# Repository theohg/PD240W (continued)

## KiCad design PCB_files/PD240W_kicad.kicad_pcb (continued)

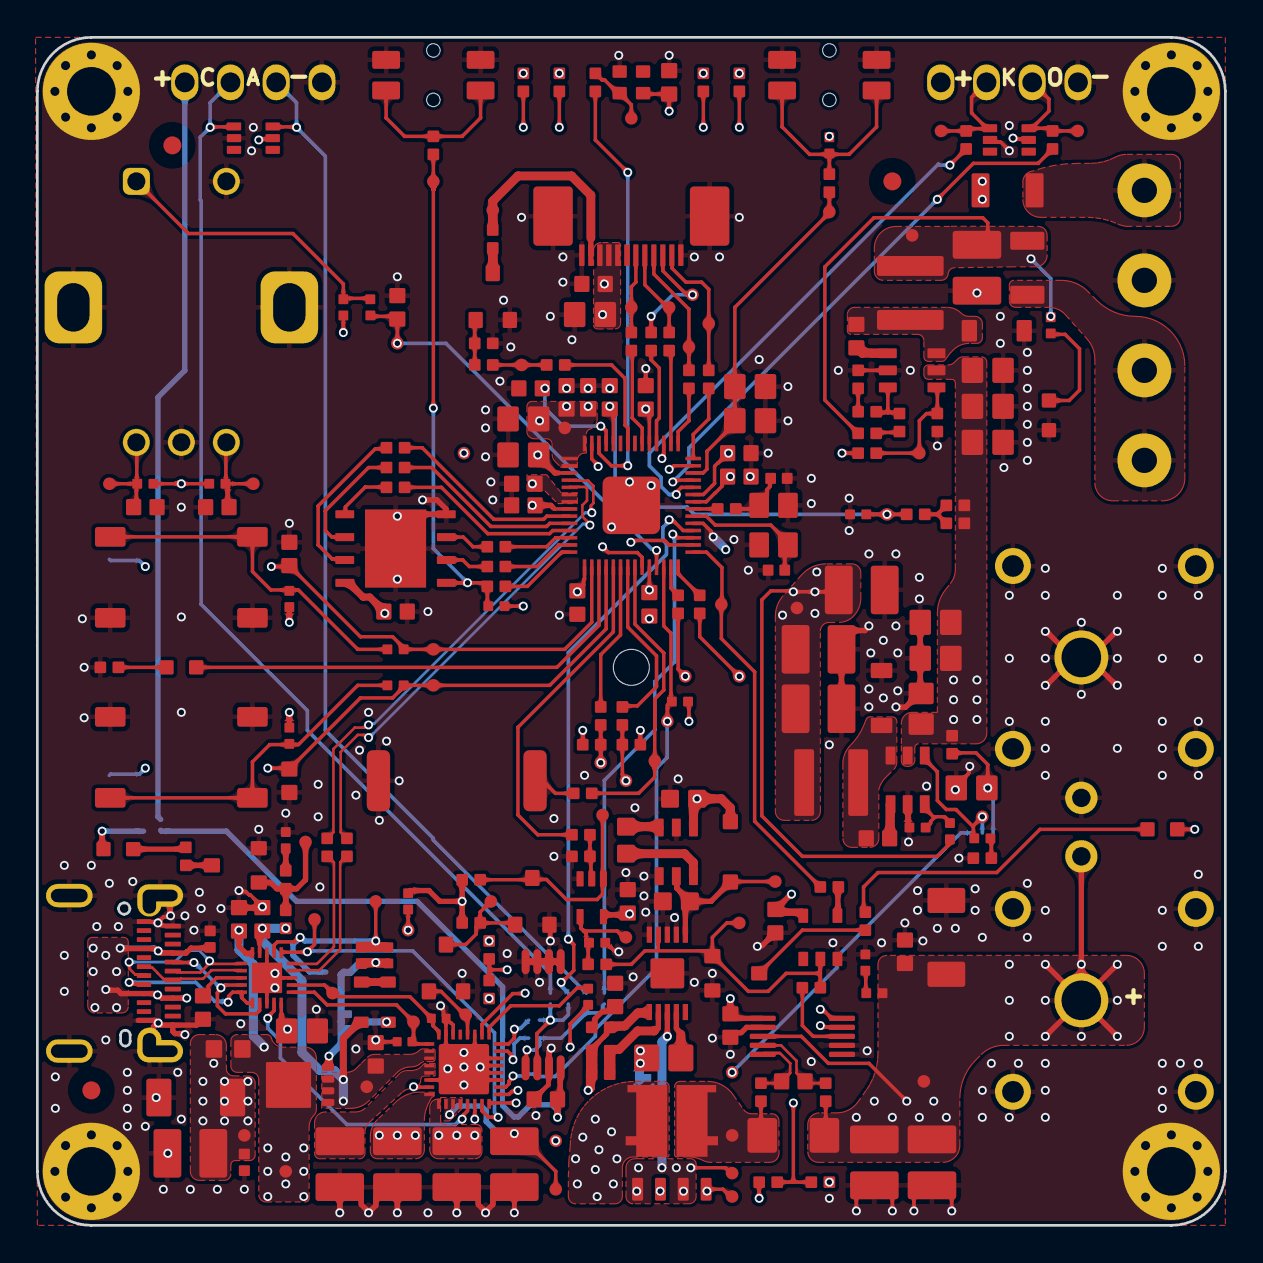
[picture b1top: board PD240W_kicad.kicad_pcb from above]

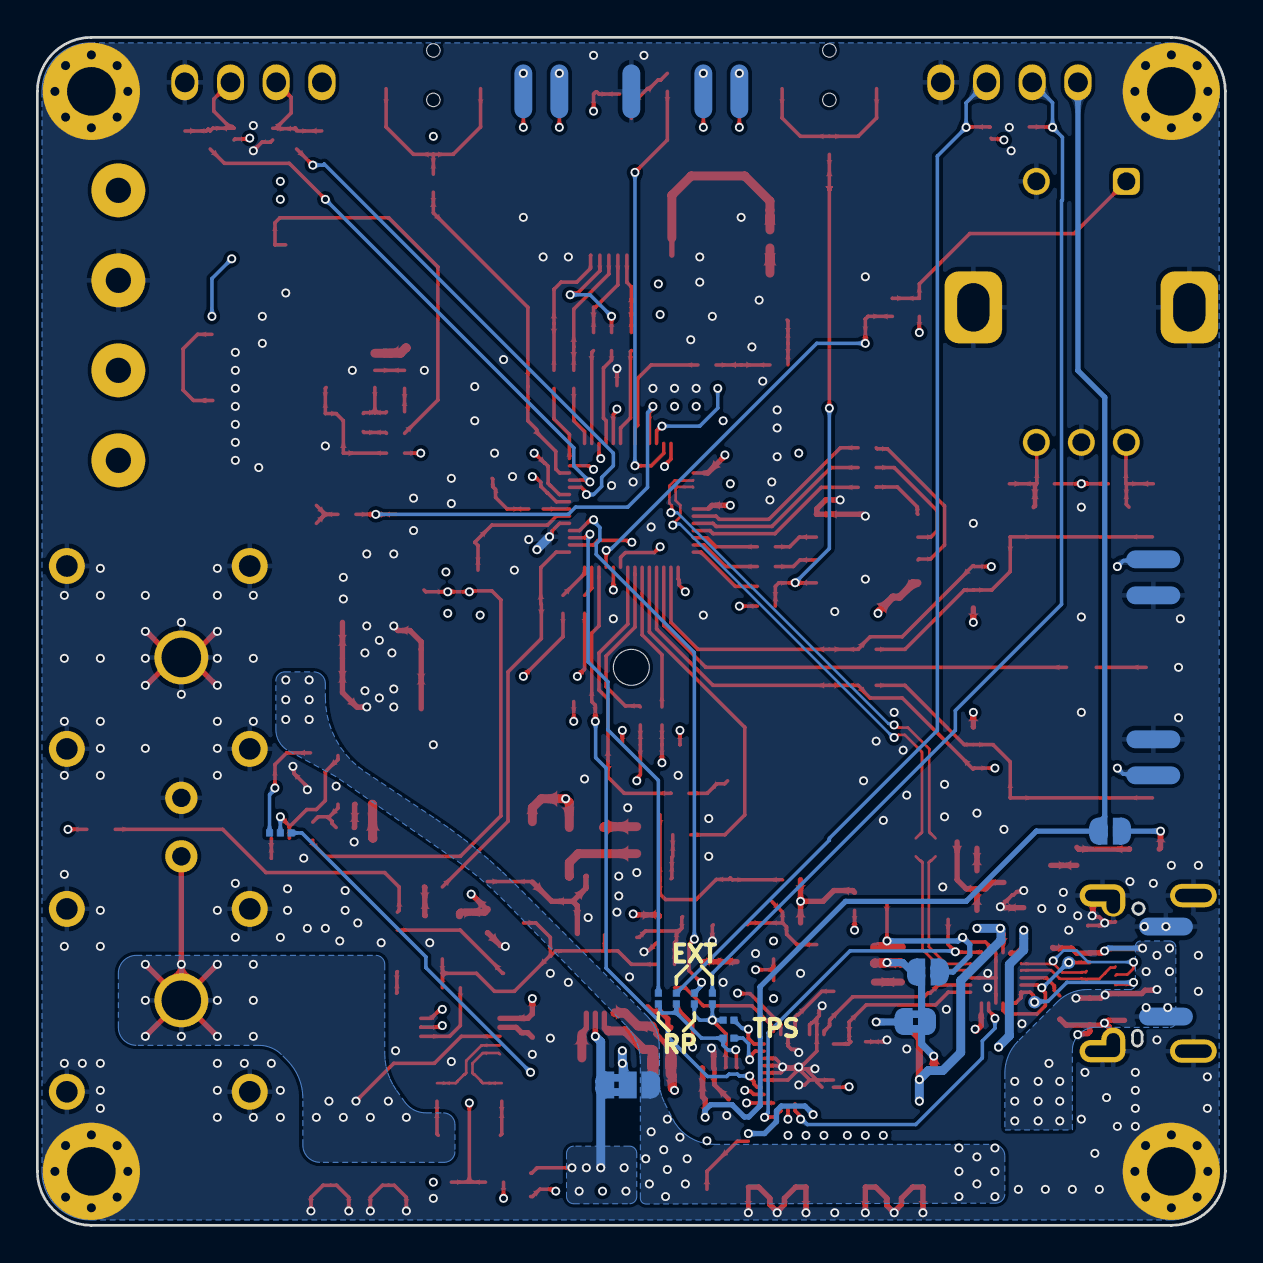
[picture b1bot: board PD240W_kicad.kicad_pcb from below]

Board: 6 copper layers, 66.0 x 66.0 mm, 299 parts (25 on the bottom side), 152 nets.

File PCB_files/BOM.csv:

,Line #,Name,Description,Designator,Quantity,LCSC,Manufacturer 1,Manufacturer Part Number 1
,2,4.7u,"Capacitor, 4.7 uF, 10%, X7S, 100V, 3225, 1210",C3,1,C913445,Murata,GCM32DC72A475KE02K
,3,100n X7R 100V,"Capacitor, 100nF, 10%, X7R, 100V, 1608, 0603","C4, C6, C8, C16, C17, C21, C22, C23, C24, C25, C26, C27, C30, C34, C35, C37, C38, C39, C40, C41, C42, C43, C44, C47, C48, C49, C50, C52, C53, C54, C55, C63",32,C15725,Samsung Electro-Mechanics,CL10B104KC8NNNC
,4,1u X7R 100V,"Capacitor, 1uF, 10%, X7R, 100V, 2012, 0805","C7, C31, C32, C33, C36, C51, C56, C57, C58, C62, C64, C65, C66",13,C5370002,YAGEO,CC0805KKX7R0BB105
,6,3.3u X5R 25V,"Capacitor, 3.3uF, 20%, X5R, 25V, 1608, 0603","C13, C14, C15",3,C5360803,CCTC,TCC0603X5R335M250CT
,9,15p COG 50V,"Capacitor, 15pF, 5%, C0G, 50V, 1005, 0402","C45, C46",2,C1548,Fenghua Electronics,0402CG150J500NT
,24,SWPA4030S220MT,FIXED IND 22UH 1A 292 MOHM SMD,L1,1,C83472,Sunlord,SWPA4030S220MT
,30,100k 1%,"Resistor, 100k, 1%, 100ppm, 1/16W, 1005, 0402","R1, R3, R14, R15, R16, R17, R21, R27, R28, R29, R75, R81, R85, R87, R88",15,C25741,UNI-ROYAL(Uniroyal Elec),0402WGF1003TCE
,36,330R 1%,"Resistor, 330R, 1%, 100ppm, 1/16W, 1005, 0402","R20, R50, R68",3,C25104,Royal Ohm,0402WGF3300TCE
,37,8m 1%,"Resistor, 8m, 1%, 50ppm, 1W, 3216, 1206",R22,1,C2988654,Milliohm,HOLLR1206-1W-8MR-1%
,34,27R 1%,"Resistor, 27R, 1%, 100ppm, 1/16W, 1005, 0402","R7, R23, R24, R26, R37, R38, R39, R40, R42, R43, R44, R45, R46, R47, R48, R49, R51, R52, R56, R57, R58, R59, R60, R61, R62, R64, R65, R66, R74",29,C138021,Yageo,RC0402FR-0727RL
,32,1k 1%,"Resistor, 1k, 1%, 100ppm, 1/16W, 1005, 0402","R5, R35, R53, R54, R55, R63, R67",7,C11702,Royal Ohm,0402WGF1001TCE
,49,SN74LVC1G17DBVR,SN74LVC1G17 Single Schmitt-Trigger Buffer,U7,1,C7836,Texas Instruments,SN74LVC1G17DBVR
,50,INA228AIDGSR,"INA240 High- and Low-Side, Bidirectional, Zero-Drift, Current-Sense Amplifier with",U8,1,C2887910,Texas Instruments,INA228AIDGSR
,52,W25Q128JVPIQ,3V 128M-BIT SERIAL FLASH MEMORY WITH DUAL/QUAD SPI,U10,1,C190862,Winbond,W25Q128JVPIQ
,35,4.7k 1%,"Resistor, 4.7k, 1%, 100ppm, 1/16W, 1005, 0402","R8, R9, R11, R12, R18, R25, R30, R84, R89, R90",10,C25900,UNI-ROYAL(Uniroyal Elec),0402WGF1003TCE
,44,LM2765,"Switched-Capacitor Voltage Converter, 40mA, input 1.8-5.5V, out =2xVIN, 50kHz, SOT-23, -40°C~+85°C",U2,1,C140270,Texas Instruments,LM2765M6X/NOPB
,47,74LVC1G08SE-7,Single 2-input AND gate,U5,1,C460522,Diodes Inc.,74LVC1G08SE-7
,8,220p X7R 50V,"Capacitor, 220pF, 10%, X7R, 50V, 1005, 0402","C19, C20",2,C296710,Samsung Electro-Mechanics,CL05B221KB5NNNC
,31,33k 1%,"Resistor, 33k, 1%, 100ppm, 1/16W, 1005, 0402","R2, R4, R33, R34, R72, R78, R79, R80, R82",9,C138003,Yageo,RC0402FR-0733KL
,25,ASWPA4035S680MT,FIXED IND 22UH 1A 292 MOHM SMD,L2,1,C340217,Sunlord,ASWPA4035S680MT
,11,BZT52C18SQ,Zener Diode 18V 200mW 5% Surface Mount SOD-323,"D2, D3",2,C2857090,JSMSEMI,BZT52C18SQ
,14,D3V3F4U6S,4-Ch 3.3V Low Cap TVS Array 0.85pF 3.5A 350mW,"D7, D10",2,C1869321,Diodes Inc.,D3V3F4U6S-7
,19,BLM18SN220TH1D,"Ferrite Bead, 120Ohm@100MHz, 25%, DCR 25mOhm, 1608, 0603",FB1,1,C710392,Murata,BLM18SN220TH1D
,39,3.9R 1%,"Resistor, 3.9R, 1%, 200ppm, 1/16W, 1005, 0402",R73,1,C2933095,FOJAN,
,38,SDNT1005X103F3950FTF,"NTC Thermistors 10k @25°C, B3950, 0.33mA max",R32,1,C95939,Sunlord,SDNT1005X103F3950FTF
,18,FSMD020-1206-R,"PTC,  30V, I_ hold 200mA, I_Trip 400mA, Imax 100A, 1206","F1, F2",2,C220145,Fuzetec,FSMD020-1206-R
,7,2.2u X7R 100V,"Capacitor, 2.2nF, 10%, X7R, 100V, 2012, 0805",C18,1,C22367838,Chinocera,
,16,MBR1H100SFT3G,"Rectifier Diode, Schottky, 1 Phase, 1A, 100V","D12, D13",2,C235757,onsemi,MBR1H100SFT3G
,1,10n X7R 100V,"Capacitor, 10nF, 10%, X7R, 100V, 1005, 0402","C1, C2, C5",3,C527014,Yageo Group,CC0402KRX7R0BB103
,5,10u X7R 63V,"Capacitor, 10uF, 10%, X7R, 63V, 3225, 1210","C9, C10, C11, C12, C28, C29, C59, C60, C61, C67",10,C437568,Murata,GRM32ER71J106KA12L
,10,SMAJ48A,"Diode, TVS, Single, Unidirectional, Vrwm max 48V, Vbr min 53.3V, Vcl max 77.4V, Irm 1uA, peak puls power 400W, C 80pF @50V, IEC61000-4-2 ESD, IEC61000-4-4 EFT, IEC61000-4-5 Surge, DO-214AC, 2.9x4.6x2.65mm, -55°C ~ 150°C","D1, D8",2,C41376401,hongjiacheng,SMAJ48A
,12,APTD1608LQBC/D,"Standard LEDs - SMD Chip LED, Package= 0603, Color = Blue","D4, D6, D9, D14",4,C5344742,Kingbright,APTD1608LQBC/D
,13,B0520LW-7-F,"Schottky Diodes & Rectifiers 20V 410mW, SMD, SOD123",D5,1,C155367,Diodes Inc.,B0520LW-7-F
,15,SK6812-EC20,"-40℃~+80℃ 0.65mA 160° 1kHz 2000V 620nm~630nm 800Kbit/s R:100mcd~200mcd Semi-transparent lens SMD,2x2mm RGB LEDs(Built-in IC) ROHS",D11,1,C2909058,OPSCO Optoelectronics,
,17,HS20HS072RX,"240x320 (2.4"") TFT-LCD panel Integrated driver (ST7789T3) and FPC",DSP1,1,C5329582,,
,20,DX07S024JJ2R1300,"USB Connector USB 3.2 Gen 2 TypeC Receptacle Horizontal SMT Body, Height 3.14 mm, 24 Contacts",J1,1,C2977282,JAE Electronics,DX07S024JJ2R1300
,21,FCR7350R,4MM PANEL SKT S16N-PC RED,J3,1,C7437326,Cliff,FCR7350R
,22,FCR7350B,4MM PANEL SKT S16N-PC BLACK,J4,1,C7437327,Cliff,FCR7350B
,23,AFC07-S12FCA-00,"0.3mm 0.5mm 12P 2mm Bottom Contact Slide Lock Surface Mount, Right Angle SMD,P=0.5mm,Surface Mount，Right Angle FFC, FPC (Flat Flexible) Connector Assemblies ROHS",J8,1,C262559,JUSHUO,
,26,FUET-9018,"-30℃~+70℃ 1V~25V 2.1mm 3V 4kHz 5mA 65dB 9mm 9mm Passive (Externally Driven) Piezoelectric SMD, 9x9mm Buzzers ROHS",PZ1,1,C391035,FUET,
,27,AGM612AP,"MOSFET, n-channel, 60V, r_ds_on 11mOhm, 10A @Ta=25°C, 50A @Tc=25°C, Vgs_th 1.6V, SMD PDFN-8 pin, (3.3x3.3x0.8mm), -55°C ~ 155°C (Tj)",Q1,1,C5349119,AGM,AGM612AP
,28,AO3404A,"MOSFET 30V 1.4W, SOT-23-3L","Q2, Q4, Q5, Q6, Q7",5,C30010,Alpha & Omega Semiconductor,AO3404A
,,SQJB90EP-T1_GE3,"Mosfet, 2 N-Channel (Dual), 80V, 30A, 48W, Rds 21mOhm @ 8A, 10V, PPAK-SO8",Q3,1,C727731,Vishay,SQJB90EP-T1_GE3
,33,10k 1%,"Resistor, 10k, 1%, ±25ppm, 1/16W, 1005, 0402","R6, R10, R13, R19, R31, R36, R41, R69, R70, R71, R76, R77, R83, R86",14,C25744,Royal Ohm,0402WGF1002TCE
,40,EVQ-PUC02K,"Small-sized Side-operational SMD Light Touch Switches with straight terminals, with boss.","S1, S2",2,C79174,Panasonic,EVQ-PUC02K
,41,PEC11R-4215F-S0024,"Rotary Encoders 15mm SHAFT w/SWITCH 24 detents, 24 PPR",S3,1,C143790,Bourns,PEC11R-4215F-S0024
,42,GT-TC120A-H120-L1,"Tactile switch SMD, black round button 12mm.","S4, S5",2,C2762973,G-Switch,GT-TC120A-H120-L1
,,5001,"Black PC Test Point, Miniature Phosphor Bronze, Silver Plating 0.040"" (1.02mm) Hole Diameter Mounting Type","TP31, TP32",2,,Keystone,5001
,43,TPD4S480RUKR,USB Type-C™ 48V EPR port protector with short-to-VBUS overvoltage and IEC ESD protection 20-WQFN -40 to 125,U1,1,C43131250,Texas Instruments,TPD4S480RUKR
,45,TPS26750,TPS26750 USB Type-C® and USB PD Controller With Integrated Power Switches,U3,1,C42166327,Texas Instruments,TPS26750SRSMR
,46,LTC7004x,Fast 60V High Side NMOS Static Switch Driver.,U4,1,C690106,Analog Devices,LTC7004EMSE#TRPBF
,48,CAT24C512YI-GT3,512 Kb I2C CMOS Serial,U6,1,C56096,onsemi,CAT24C512YI-GT3
,51,RP2040,ARM® CortexÂ-M0+ - Microcontroller IC 32-Bit Dual-Core 133MHz External Program Memory 56-QFN (7x7),U9,1,C2040,Raspberry Pi,RP2040
,53,LMR16006XDDCR,"LMR16006 SIMPLE SWITCHER® 60 V 0.6 A Buck Regulators With High Efficiency ECO mode, 600mA, input 4-65V, out 4-65V, 700kHz, SOT-6, -40°C~+125°C","U11, U12",2,C87080,Texas Instruments,LMR16006XDDCR
,54,ABM8-272-T3,Crystal 12MHz 10pF 30ppm -40C +85C,Y1,1,C20625731,Abracon,ABM8-272-T3

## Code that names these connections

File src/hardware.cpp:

#include "hardware.h"
#include "config/app_config.h"
#include "utils/logging.h"
#include "config/version.h"
#include "utils/tps_eeprom_loader.h"

Hardware hw;

Hardware::Hardware() :
    btn1(Board::PIN_BTN_1, ButtonPull::PULL_NONE, 10, true),
    btn2(Board::PIN_BTN_2, ButtonPull::PULL_NONE, 10, true),
    btnEnc(Board::PIN_ENC_BTN, ButtonPull::PULL_NONE, 50, true),
    overcurrentAlert(Board::PIN_SWITCH_EN_READ, IOMode::INPUT),
    pdInterrupt(Board::PIN_USB_PD_IRQ, IOMode::INPUT),
    encoder(Board::PIN_ENC_A, Board::PIN_ENC_B),
    buzzer(Board::PIN_BUZZER),
    rgbLed(Board::PIN_RGB_LED, pio0, Board::LED_IS_RGBW),
    en17v(Board::PIN_17V_EN, IOMode::OUTPUT),
    loadSwitch(Board::PIN_SWITCH_EN, IOMode::OUTPUT),
    pdController(i2c0, Board::I2C_ADDR_TPS26750),
    powerMonitor(i2c0, Board::I2C_ADDR_INA228, Board::INA228_SHUNT_RESISTOR, Board::INA228_MEASUREMENT_MAX_CURRENT, Board::INA228_SHUNT_TEMPCO_PPM),
    display(spi0, Board::PIN_LCD_CS, Board::PIN_LCD_DC, Board::PIN_LCD_RST, Board::PIN_LCD_BL)
{}

void Hardware::init() {
    // Short delay to let TPS26750 start up - actual PD negotiation is handled
    // adaptively during the boot screen via pdManager.waitForPdos()
    sleep_ms(50);
    stdio_init_all();

    LOG_SEPARATOR();
    LOG_INFO("%s %s - %s", Version::PRODUCT_NAME, Version::PRODUCT_SUBTITLE, Version::FIRMWARE_VERSION);
    LOG_SEPARATOR();

    // =========================================================================
    // Communication Bus Init
    // =========================================================================

    // I2C0 (400kHz) - for INA228 and TPS26750
    i2c_init(i2c0, Board::I2C_SPEED_HZ);
    gpio_set_function(Board::PIN_I2C_SDA, GPIO_FUNC_I2C);
    gpio_set_function(Board::PIN_I2C_SCL, GPIO_FUNC_I2C);

    // SPI0 (10MHz) - for ST7789 display
    spi_init(spi0, Board::SPI_SPEED_HZ);
    spi_set_format(spi0, 8, SPI_CPOL_1, SPI_CPHA_1, SPI_MSB_FIRST);
    gpio_set_function(Board::PIN_LCD_SCK, GPIO_FUNC_SPI);
    gpio_set_function(Board::PIN_LCD_MOSI, GPIO_FUNC_SPI);

    // =========================================================================
    // Peripheral Driver Init
    // =========================================================================

    // Simple drivers (no external communication)
    encoder.init();
    buzzer.init();
    LOG_HW_INIT("ADC", adc.init());

    // Display (SPI)
    LOG_HW_INIT("ST7789 Display", display.init());

    // I2C devices
    if (pdController.init()) {
        LOG_INFO("TPS26750 PD Controller initialized successfully with FW %s",
                 Version::TPS_FIRMWARE_VERSION);
    } else {
        LOG_ERROR("TPS26750 PD Controller initialization FAILED");
    }
    _power_monitor_ok = powerMonitor.init();
    if (_power_monitor_ok) {
        if (!powerMonitor.setADCRange(Board::INA228_USE_LOW_ADC_RANGE)) {
            LOG_WARN("INA228 ADC range configuration failed");
        }
        LOG_INFO("INA228 Power monitor initialized successfully with FW %s",
                 Version::INA_FIRMWARE_VERSION);
    } else {
        LOG_ERROR("INA228 Power monitor initialization FAILED - load switch disabled "
                  "(no current sensing / overcurrent protection)");
    }

    // RGB LED (PIO)
    LOG_HW_INIT("SK6812 RGB LED", rgbLed.init());

    // =========================================================================
    // Initial Output States
    // =========================================================================
    loadSwitch.off();
    rgbLed.setColor(LedColor::BLUE, AppConfig::RGB_LED_BRIGHTNESS_NORMAL);
}

void Hardware::update() {
    // Update drivers that need periodic polling
    rgbLed.update();
}

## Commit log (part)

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2026-01-22 Stop tracking user-specific VS Code configs
2026-01-22 Cleaned code. PDO reading working
2026-01-26 Added Overcurrent protection methode, cleaned hardware init, added info log for succesful init, spearated interrupts from main, added blink method for GPIO
2026-01-26 Working with 5V but not 15V. Flashing full flash binary with C++ code.
2026-01-26 Finally found a robust way of making PCB work without debugger atatched.
2026-01-26 Moving to phase 3, reorganized structure, prepared plan for phase 3
2026-01-26 First version of the state machine and UI working
2026-01-27 Working UI, no flickering, fixed conctracts dispaly, and more
2026-01-27 Working UI, no flickering, fixed conctracts dispaly, and more, updated documentation
2026-01-27 Working UI, no flickering, fixed conctracts dispaly, and more, updated documentation_ 2
2026-01-27 Implemented overtemperature protection, cleaned UI, added synapticon logo
2026-01-28 Fixed RGB LED behavior during fault, and implmented EEPROM flashing feature
2026-01-28 PPS support implemented, not tested
2026-01-29 Improved encoder rotation click logic, added scaling for current and voltage measurements
2026-01-29 Cleaned UI, fixed flickering, cleaned bootup, added melody, cleaned about
2026-01-29 Cleaned logo, cleaned UI, added beeps, added precise current settings, updated doc
2026-01-29 Added settings menu, auto-dim
2026-02-02 Cleaned repo, cleaned code, added PCB files, stl and 3d models, prepared next steps
2026-02-02 Updated .gitignore.
2026-02-02 Added USB-PD norm badge, added energy monitoring, added melody selection, added auto dim config, added auto output on config, fixed screen flicker in settings, fixed temeparture display clearing, add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
2026-02-03 Fixed long encoder button press causing double clicks, added color helpers for rgb led, cleaned auto-dim variables, fixed PD badge not showing on boot, fixed setting change full redraw
2026-02-06 Fixed buzzer beep for overtemp, fixed menu flickering, removed noise in current and wattage measurements, cleaned overctemp screen, and few more minor fixes
2026-02-07 Cleaned UI, cleaned about menu, early readme, added CI, added release workflow, added current contract highlight
2026-02-07 Added images & gif to readme, fixed as best as possible overcurrent screen and overtemp screens
2026-02-07 Improved README
2026-02-09 Updated README, added gerbers and liscence [skip ci]
2026-02-19 [Repo][Modified] README [skip ci]
2026-03-16 Added KiCad PCB files, updated licence, updated README [skip ci]
2026-03-16 Updated README [skip ci]
2026-03-22 Fixed looping issue when scrolling with many contracts available, can go from 48V to 36V to 28V but cannot go back to SPR
2026-03-22 LG still broken, no more 48V detected, but can navigate between 5-20V on the framework
2026-03-22 Fixed 48V neg on refresh bug on main menu, LG still not working
2026-03-22 Fixed AVS and duplicated contracts, added EPR and AVS badges
2026-03-24 Implemented AVS tuning,added EPR badge, improved PPS and AVS tuning, cleaned code, updated doc
2026-03-24 Implemented a sketchy CC mode, improved INA228 library with true power math core, and ppm compensation, tried switching mode CC (fail) and reduced amount of EEPROM save
2026-03-29 Finished implemented CC mode, improved AVS tuning, added safe exit AVS feature
2026-03-29 Cleaned code (magic numbers, dead code, duplicates, missing inits)
2026-03-30 Implemented CLI control (not tested)
2026-04-27 Added possibility to disable Auto-Dim, fix AVS current bug at PDO voltages, fixed display issue for current and voltage selection
2026-04-27 Fix voltage spike at reboot when in last V used mode
2026-04-30 Rebranded the UI to blue/magenta and PD240W logo. Fix persistent bip in mute mode when exiting the voltage selection menu. Fixed AVS/EPR/PPS badges fake persistence after reboot with a different char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
2026-05-18 Rounded loading bars with gradient, rounded highlight bar, improved EEPROM flashing screens showing the progress, detect SPR AVS contracts and identifies charger as PD3.2, centered highlight bar on t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
2026-05-19 Fixed SPR and PPS negotiation, and fixed AVS negotiation. However did not fix SPR AVS, and there are bugs in the transitions from EPR to SPR
2026-05-19 Log PD revision only when it changes, to avoid noise in serial terminal
2026-05-20 fixed exit from EPR fixed PDO to lower voltage that always go to 5V and not the correct fixed PDO (no 9, 15 or 20), fixed exit EPR AVS to SPR AVS that cause reboot
2026-05-20 Fixed bug were EPR badge was appearing on main screen for SPR AVS
2026-05-20 Imroved naming of states transitions in the logs
2026-05-20 Smoothed color gradient, moved remote badge away from logo on the main menu, renamed setLastPpsVoltageMv because it was confusing, display more settings from flash at boot
2026-05-26 Integrate INA228 multiplatform library as submodule and remove local driver
    - add external/ina228_multiplatform as git submodule
    - switch CMake to build INA228 sources from submodule
    - update hardware include and constructor usage for bus-first INA228 API
    - remove duplicated in-tree INA228 implementation
    - update README and notes for submodule-based build flow
    - update CI/release workflows to checkout submodules recursively
2026-05-30 Add charger diagnostics and smarter cable inference
    Add an About This Charger diagnostics view with live PD revision, CC orientation, charger identity, QC inference, and source power reporting.
    Extend the TPS26750 driver with GPPI and MBRd helpers so the firmware can request Manufacturer Info and expose controller status to higher layers.
    Refine cable rating detection to distinguish confirmed 5A cables from likely 3A and charger-limited unknown cases, avoiding false positives from PPS-only >3A advertisements.
2026-05-30 Fix programmable adjust cursor restore
    Reuse the active PPS or AVS target when reopening the selected APDO from the voltage selection menu, instead of resetting the cursor to the middle of the range.
    Keep the quick-adjust and menu entry paths aligned through a shared programmable target initializer that clamps to the current APDO bounds.
    Reduce the encoder long-press threshold from 700ms to 300ms so PPS and AVS quick adjust feels more responsive.
2026-05-30 Expose pinned INA version and improve about screens
2026-05-30 Refine startup contract restore and boot logging
    Make LAST_USED restore charger-agnostic by saving explicit contract metadata and matching by intent instead of blindly trusting PDO indices.
    Defer >20V restore targets until EPR PDOs appear, retry after EPR discovery, and fall back cleanly on non-EPR chargers.
    Clean up boot and polling logs, keep about screens alive on encoder activity, and include the menu auto-return timeout adjustment.
2026-05-30 Stabilize PPS and AVS tuning feedback
    Keep programmable contract state alive while PPS/AVS requests are still settling so Vset and badge state do not disappear on first entry.
    Retain PPS/AVS tracking through normal regulation error, speed up unconverged tuning retries, and restore 20mV PPS single-detent steps.
2026-06-01 Prepare firmware 2.0 cleanup
2026-06-01 Add OFF current limit mode
2026-06-01 Increased max current reading from INA from 5.0A to 5.12A
2026-06-01 Updated README for release v2.0.0
2026-06-01 Add v2.0.0 changelog and release notes
2026-06-17 Fit more contracts in voltage select menu
    Pull the PDO list up to the header and raise the visible row cap
    from 8 to 10, reducing scrolling on chargers with many contracts.
2026-06-17 Release v2.0.1
    Bump firmware version and add 2.0.1 changelog entry.
2026-06-25 Migrate TPS26750 driver to shared multiplatform submodule
    Replace the in-tree tps26750 driver with the external
    tps26750_multiplatform submodule and adopt its TPS26750_* types
    across pd_manager, state_machine, hardware, and the display.
    Add a TPS FW version line to the About screen and tidy its
    spacing/column layout.
2026-06-25 Release v2.0.2
2026-06-29 Lower PD disconnect VBUS threshold to 3.3V
2026-06-30 Push TPS26750 PD config over I2C (burst mode), drop EEPROM dependency
    Stream the patch bundle + app config directly from the RP2040 over I2C at
    boot using the TI burst-mode tasks (PBMs -> burst -> PBMc), so an EEPROM-less
    board can transition the TPS26750 from PTCH to APP mode.
    - Derive the low region (patch + config) from the validated full-flash image. Sourcing both EEPROM and burst paths from one image keeps them identical.
    - Issue the startup pre-boot contract request after the patch reaches APP mode
    (boot stage 0), not in main() where the TPS is still in PTCH.
2026-06-30 Make flash size configurable instead of hardcoded 2MB
    Settings storage offset and About-screen flash usage now derive from
    PICO_FLASH_SIZE_BYTES (set to the real 16MB/128Mbit chip) instead of
    an assumed 2MB, so both reflect the actual hardware. The value is wired
    into both the linker flash region and the C compile definitions so
    they stay in sync.
2026-06-30 Fix Max Power showing 0W for non-PD chargers, bump TPS26750 driver to v1.0.1
